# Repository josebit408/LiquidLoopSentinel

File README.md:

# LiquidLoopSentinel

LiquidLoopSentinel is a Raspberry Pi Pico-based printed circuit board designed to monitor coolant temperature, flow, leaks, and electrical conditions while providing visual and audible fault alerts.

## Overview

LiquidLoopSentinel is a custom monitoring printed circuit board intended for liquid-cooled computing systems and artificial intelligence hardware test benches.

The board integrates multiple sensors with a Raspberry Pi Pico to monitor the condition of a liquid-cooling loop and detect problems such as:

- Abnormal coolant temperature
- Reduced or interrupted coolant flow
- Liquid leakage
- Electrical power abnormalities

When the system detects a fault, it can provide visual status indications through light-emitting diodes and an audible warning through a buzzer.

## Features

- Raspberry Pi Pico controller
- Two temperature sensor inputs
- Coolant flow sensor input
- Leak sensor input
- INA219 voltage and current monitoring interface
- Inter-Integrated Circuit communication
- Flow sensor signal conditioning
- Leak sensor pull-up circuitry
- Three status indicators:
  - System operating normally
  - Warning condition
  - Leak detected
- Transistor-driven buzzer
- Dedicated test points
- Separate 5-volt flow sensor power input
- Ground plane
- Through-hole component design for prototyping and manual assembly

## System Architecture

```text
                    Liquid-Cooling Loop
                           |
          +----------------+----------------+
          |                |                |
     Temperature          Flow             Leak
       Sensors            Sensor           Sensor
          |                |                |
          +----------------+----------------+
                           |
                           v
                  Raspberry Pi Pico
                           |
                 System Health Analysis
                           |
             +-------------+-------------+
             |             |             |
             v             v             v
          OK LED       Warning LED    Leak LED
                                           |
                                        Buzzer
```

## Hardware

### Microcontroller

The system is designed around the **Raspberry Pi Pico**.

The Pico receives sensor signals, evaluates the condition of the cooling loop, and controls the board's visual and audible warning indicators.

### Temperature Monitoring

Two temperature sensor connections are provided:

- `TEMP_IN`
- `TEMP_OUT`

Both connections share the `TEMP_ONEWIRE` data bus and use a 4.7-kilohm pull-up resistor connected to 3.3 volts.

This configuration allows the system to measure coolant temperature at two locations within the cooling loop.

### Flow Monitoring

The flow sensor interface provides the following connections:

- `+5V_FLOW`
- `FLOW_SENSOR_RAW`
- `GND`

A resistor-divider network conditions the raw flow sensor signal before it reaches the Raspberry Pi Pico as `FLOW_PULSE`.

### Leak Detection

A dedicated leak sensor connector provides the following connections:

- `LEAK_DETECT`
- `GND`

A 100-kilohm pull-up resistor connects the leak detection signal to 3.3 volts.

### Electrical Monitoring

An INA219 interface provides the following connections:

- `+3V3`
- `GND`
- `I2C0_SDA`
- `I2C0_SCL`

This interface supports voltage, current, and power monitoring through a compatible INA219 module.

### Status Indicators

The printed circuit board includes three status indicators:

| Indicator | Purpose |
|---|---|
| `LED_OK` | Indicates normal operation |
| `LED_WARN` | Indicates a warning condition |
| `LED_LEAK` | Indicates that a leak has been detected |

Each light-emitting diode uses a 330-ohm current-limiting resistor.

### Audible Alert

A buzzer provides an audible warning when the system detects a fault.

The Raspberry Pi Pico controls the buzzer through an NPN transistor stage, preventing the microcontroller's general-purpose input and output pin from directly driving the buzzer load.

### Test Points

The board includes dedicated test points for the following signals:

- `+3V3`
- `GND`
- `FLOW_PULSE`
- `LEAK_DETECT`

These test points allow important system signals to be measured during testing, validation, and troubleshooting.

## Printed Circuit Board

The current hardware revision is:

**LiquidLoopSentinel Revision A**

The printed circuit board is currently in the prototype and design-validation stage.

Current design characteristics include:

- Two-layer printed circuit board
- Through-hole components
- Front and back copper routing
- Bottom-layer ground plane
- Raspberry Pi Pico socket headers
- Dedicated sensor connectors
- Dedicated test points

## Repository Structure

```text
LiquidLoopSentinel/
|
├── README.md
├── LICENSE
|
├── hardware/
│   └── kicad/
│       ├── LiquidLoopSentinel_RevA.kicad_pro
│       ├── LiquidLoopSentinel_RevA.kicad_sch
│       └── LiquidLoopSentinel_RevA.kicad_pcb
|
├── manufacturing/
│   └── RevA/
│       ├── gerbers/
│       ├── drill/
│       └── bom/
|
├── firmware/
│   └── pico/
|
├── docs/
│   └── images/
|
└── mechanical/
    └── 3d/
```

## Development Status

**Revision A: In Development**

Current progress:

- [x] System architecture
- [x] Schematic design
- [x] Printed circuit board component placement
- [x] Printed circuit board routing
- [x] Ground plane
- [x] Design Rules Check
- [x] Schematic and printed circuit board parity check
- [ ] Final component pinout verification
- [ ] Connector orientation verification
- [ ] Silkscreen cleanup
- [ ] Mounting holes
- [ ] Final manufacturing review
- [ ] Gerber file generation
- [ ] Printed circuit board fabrication
- [ ] Board assembly
- [ ] Hardware validation
- [ ] Raspberry Pi Pico firmware

## Project Goal

The goal of LiquidLoopSentinel is to create a low-cost, modular hardware monitoring platform that can detect cooling-system failures before they damage sensitive computing equipment.

## Development Tools

- KiCad 10
- Raspberry Pi Pico
- C, C++, or MicroPython
- Git
- GitHub

## Disclaimer

LiquidLoopSentinel Revision A is an experimental engineering prototype that has not yet completed hardware validation. It should not be used as the sole protection mechanism for safety-critical systems or high-value equipment.

## Author

**Jose Luis Zaragoza-Calderon Jr.**

Computer Engineering

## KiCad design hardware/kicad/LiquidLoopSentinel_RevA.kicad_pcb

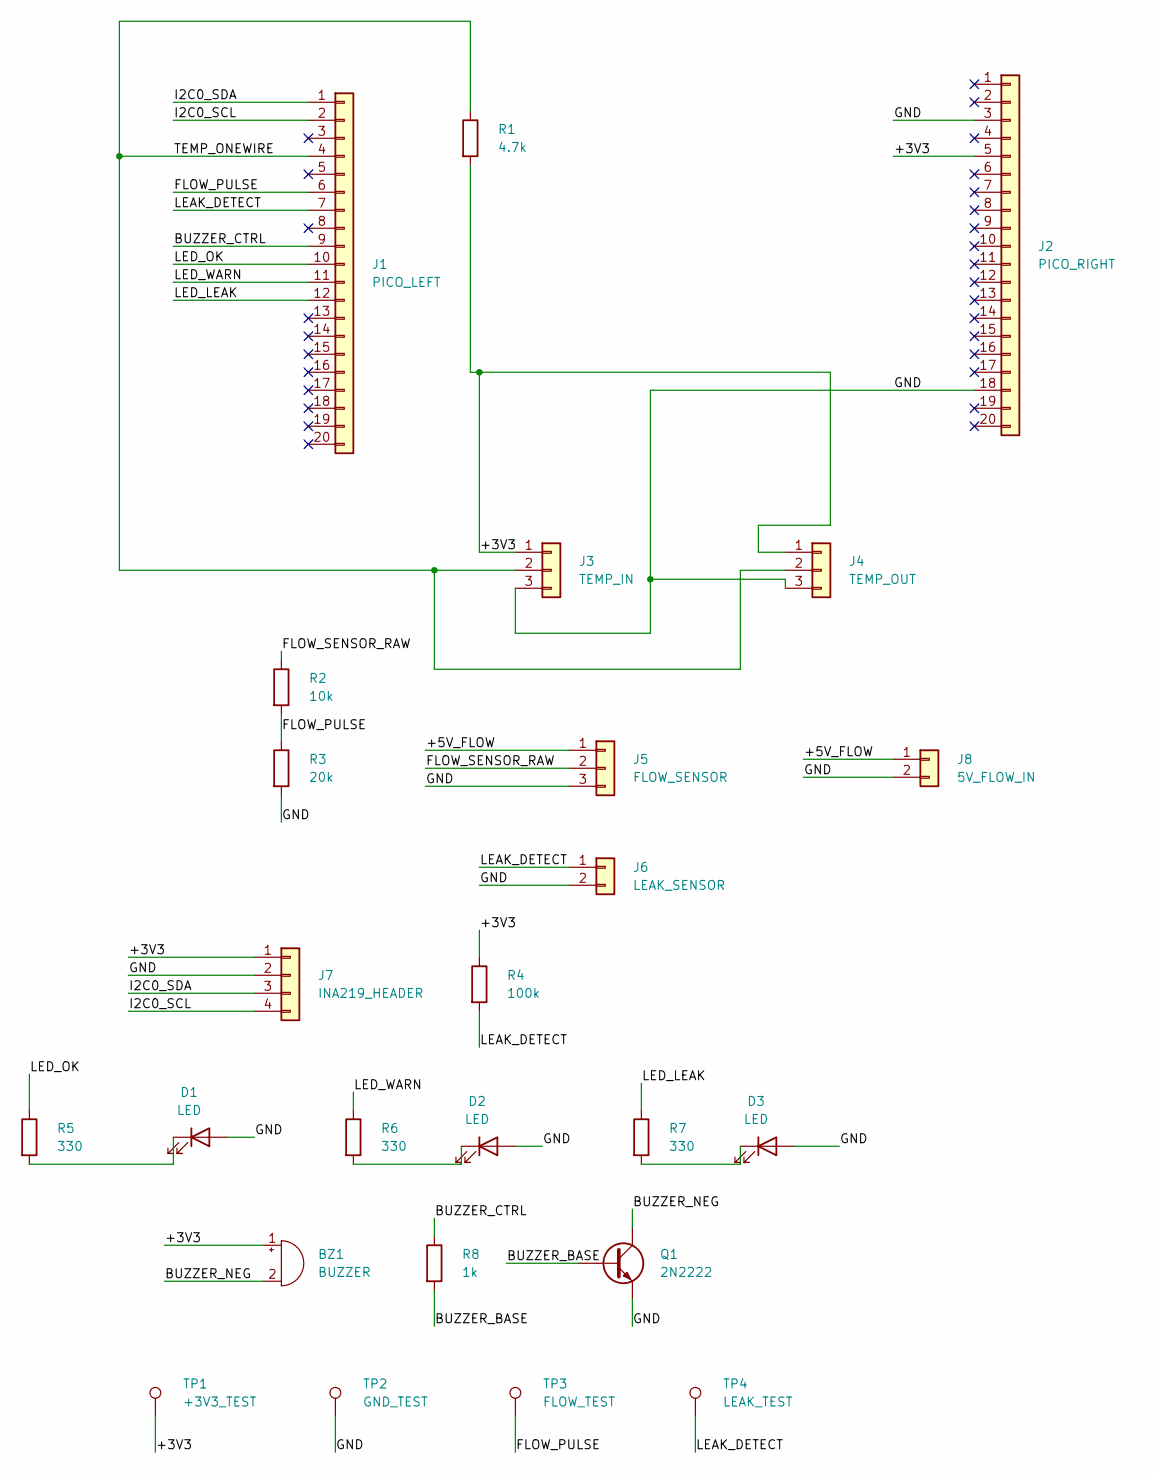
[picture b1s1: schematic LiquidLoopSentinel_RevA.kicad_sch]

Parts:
BZ1: BUZZER; Buzzer_12x9.5RM7.6
D1, D2, D3: LED; LED_D5.0mm
J1: PICO_LEFT; PinSocket_1x20_P2.54mm_Vertical
J2: PICO_RIGHT; PinSocket_1x20_P2.54mm_Vertical
J3: TEMP_IN; PinHeader_1x03_P2.54mm_Vertical
J4: TEMP_OUT; PinHeader_1x03_P2.54mm_Vertical
J5: FLOW_SENSOR; PinHeader_1x03_P2.54mm_Vertical
J6: LEAK_SENSOR; PinHeader_1x02_P2.54mm_Vertical
J7: INA219_HEADER; PinHeader_1x04_P2.54mm_Vertical
J8: 5V_FLOW_IN; PinHeader_1x02_P2.54mm_Vertical
Q1: 2N2222; TO-92_Inline
R1: 4.7k; R_Axial_DIN0207_L6.3mm_D2.5mm_P7.62mm_Horizontal
R2: 10k; R_Axial_DIN0207_L6.3mm_D2.5mm_P7.62mm_Horizontal
R3: 20k; R_Axial_DIN0207_L6.3mm_D2.5mm_P7.62mm_Horizontal
R4: 100k; R_Axial_DIN0207_L6.3mm_D2.5mm_P7.62mm_Horizontal
R5, R6, R7: 330; R_Axial_DIN0207_L6.3mm_D2.5mm_P7.62mm_Horizontal
R8: 1k; R_Axial_DIN0207_L6.3mm_D2.5mm_P7.62mm_Horizontal
TP1: +3V3_TEST; TestPoint_THTPad_D1.0mm_Drill0.5mm
TP2: GND_TEST; TestPoint_THTPad_D1.0mm_Drill0.5mm
TP3: FLOW_TEST; TestPoint_THTPad_D1.0mm_Drill0.5mm
TP4: LEAK_TEST; TestPoint_THTPad_D1.0mm_Drill0.5mm

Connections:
/+3V3: BZ1.1 (+), J2.5, J3.1, J4.1, J7.1, R1.2, R4.1, TP1.1 (1_1)
/+5V_FLOW: J5.1, J8.1
/BUZZER_BASE: Q1.1 (B), R8.2
/BUZZER_CTRL: J1.9, R8.1
/BUZZER_NEG: BZ1.2 (-), Q1.2 (C)
/FLOW_PULSE: J1.6, R2.2, R3.1, TP3.1 (1_1)
/FLOW_SENSOR_RAW: J5.2, R2.1
/GND: D1.2 (A), D2.2 (A), D3.2 (A), J2.3, J2.18, J3.3, J4.3, J5.3, J6.2, J7.2, J8.2, Q1.3 (E), R3.2, TP2.1 (1_1)
/I2C0_SCL: J1.2, J7.4
/I2C0_SDA: J1.1, J7.3
/LEAK_DETECT: J1.7, J6.1, R4.2, TP4.1 (1_1)
/LED_LEAK: J1.12, R7.1
/LED_OK: J1.10, R5.1
/LED_WARN: J1.11, R6.1
/TEMP_ONEWIRE: J1.4, J3.2, J4.2, R1.1
unnamed: D1.1 (K), R5.2
unnamed: D2.1 (K), R6.2
unnamed: D3.1 (K), R7.2

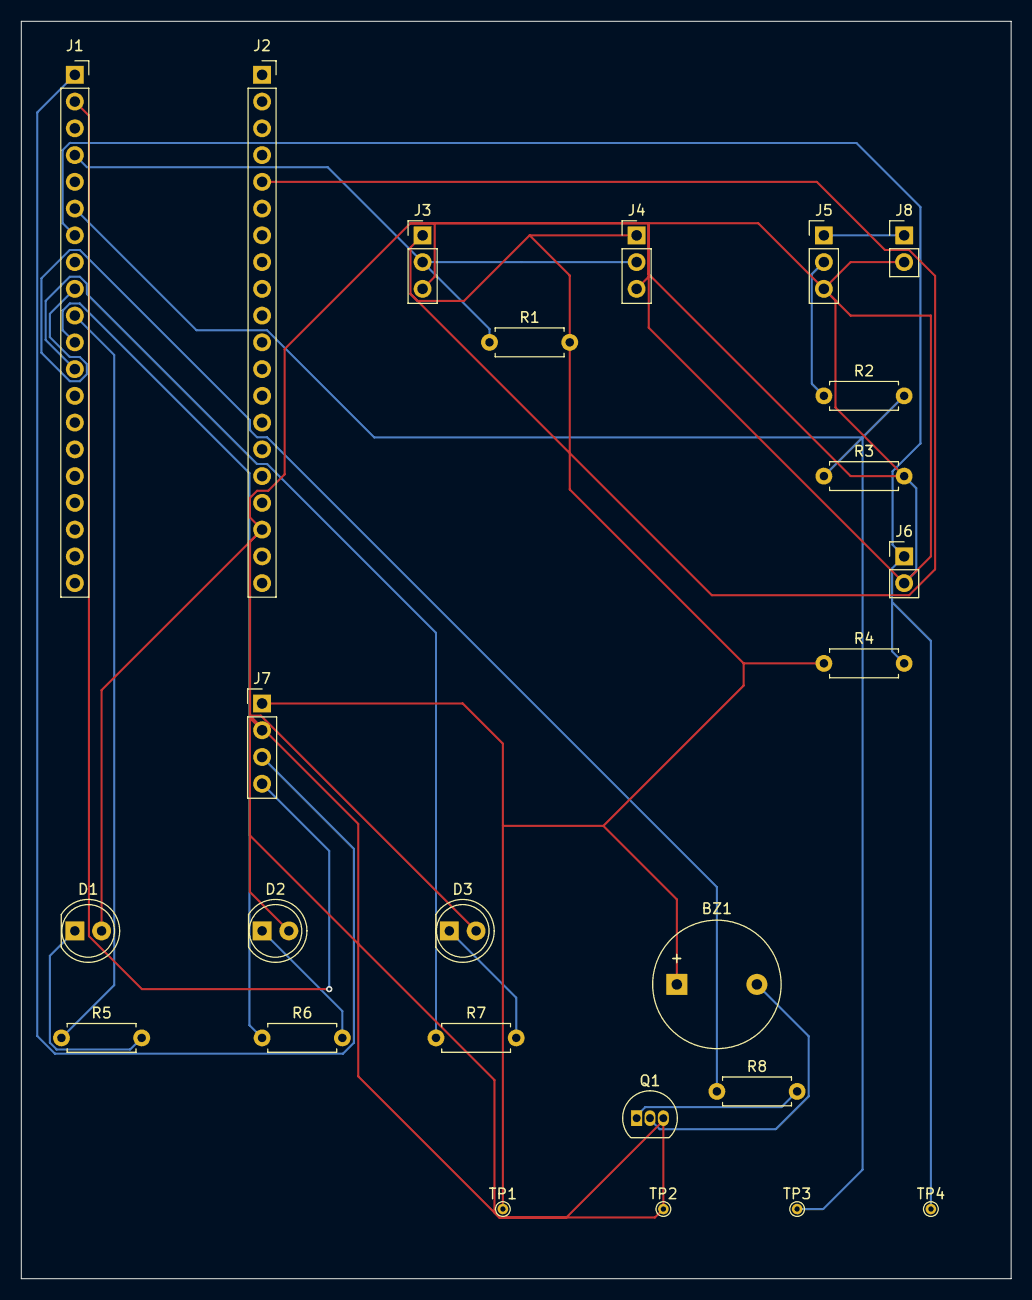
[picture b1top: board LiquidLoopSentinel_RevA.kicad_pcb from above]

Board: 2 copper layers, 94.0 x 119.4 mm, 25 parts (0 on the bottom side), 18 nets.
